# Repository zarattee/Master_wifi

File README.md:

# Master_wifi
 centro de modulo wifi

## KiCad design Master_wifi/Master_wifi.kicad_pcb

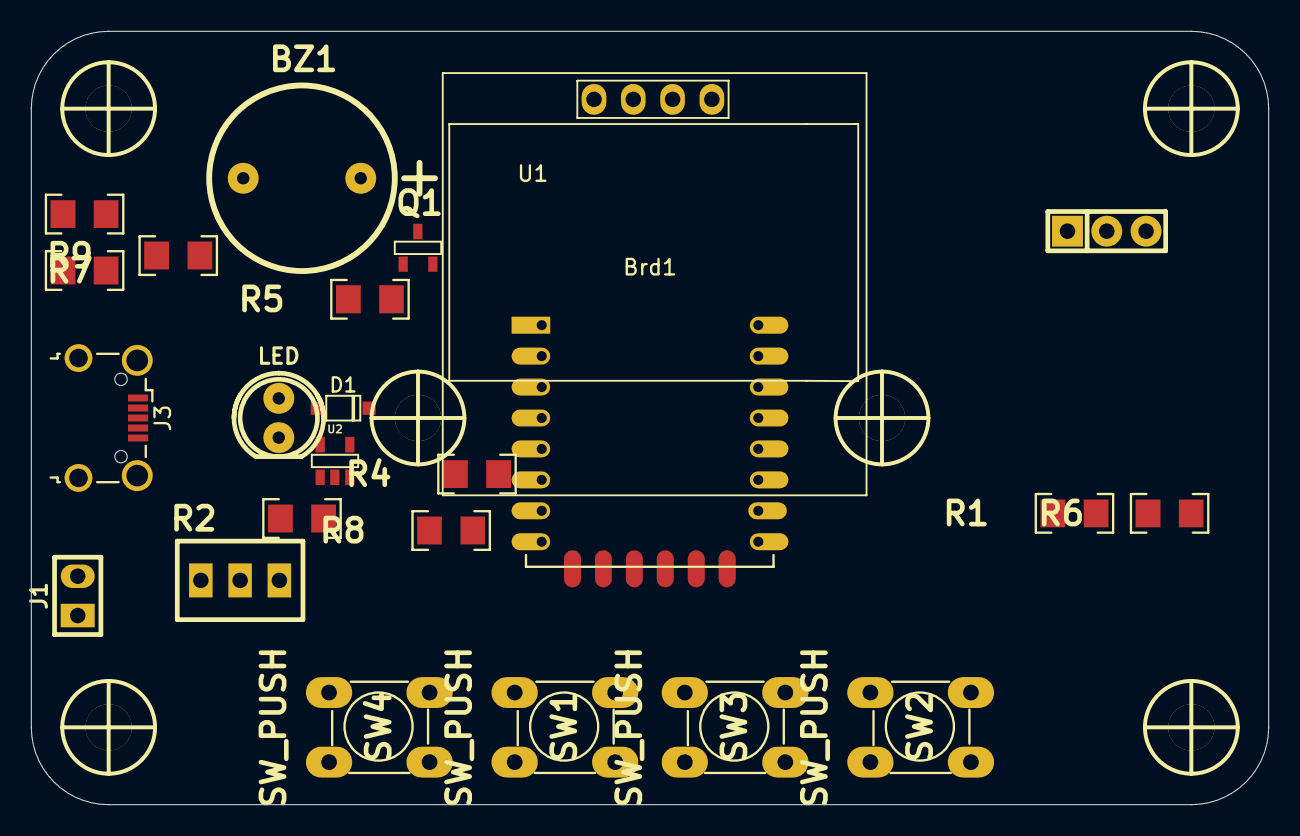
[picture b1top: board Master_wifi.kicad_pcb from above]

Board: 2 copper layers, 80.0 x 50.0 mm, 30 parts (0 on the bottom side), 13 nets, no tracks yet.

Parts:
BZ1: Buzzer; Buzzer_12mm
Brd1: SSD1306; 128x64OLED
D1: DIODE; sod123
H1, H2, H3, H4, H5, H6: Mounting_Hole; hole_3mm
J1: HEADER_2; Pin_strip_2
J2: Conn_01X03; Pin_Strip_3
J3: USB_OTG; USB_Micro-B_Wuerth_629105150521_CircularHoles
LED1: LED; led_5mm_red
Q1: 2N7002; SOT23
R1, R2, R3, R4, R5, R6, R7, R8, R9: R; R_1206
SW1, SW2, SW3, SW4: SW_PUSH; Pulsador_TH_4
SW5: SW_SPDT; SW_SPDT_TH_100Mils_VERTICAL
U1: ESP-12E
U2: MCP73831-2-OT; SOT-23-5

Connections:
/ABAJO-: R4.2, SW4.3, SW4.4
/ARRIBA+: R3.2, SW3.3, SW3.4
/BUZZER: Q1.1, R5.1, U1.10
/MODO: R1.2, SW1.3, SW1.4
/SELEC: R2.2, SW2.3, SW2.4
GND: Brd1.1, J1.1, J2.3, J3.5, J3.6, Q1.3, R5.2, R7.2, R8.2, SW1.1, SW1.2, SW2.1, SW2.2, SW3.1, SW3.2, SW4.1, SW4.2, U1.9, U2.2
unnamed: BZ1.2, D1.1, Q1.2
unnamed: J3.1, R9.1, U2.4
unnamed: J1.2, SW5.1, SW5.2
unnamed: LED1.1, R9.2
unnamed: LED1.2, U2.1
unnamed: R8.1, U2.5
VCC: BZ1.1, Brd1.2, D1.2, J2.1, R1.1, R2.1, R3.1, R4.1, R6.1, R6.2, R7.1, SW5.3, U1.8, U2.3

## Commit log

2020-11-14 Initial commit
    placa de acceso en general.
    conectividad wifi
    i2c
    uso de de botones para el control
